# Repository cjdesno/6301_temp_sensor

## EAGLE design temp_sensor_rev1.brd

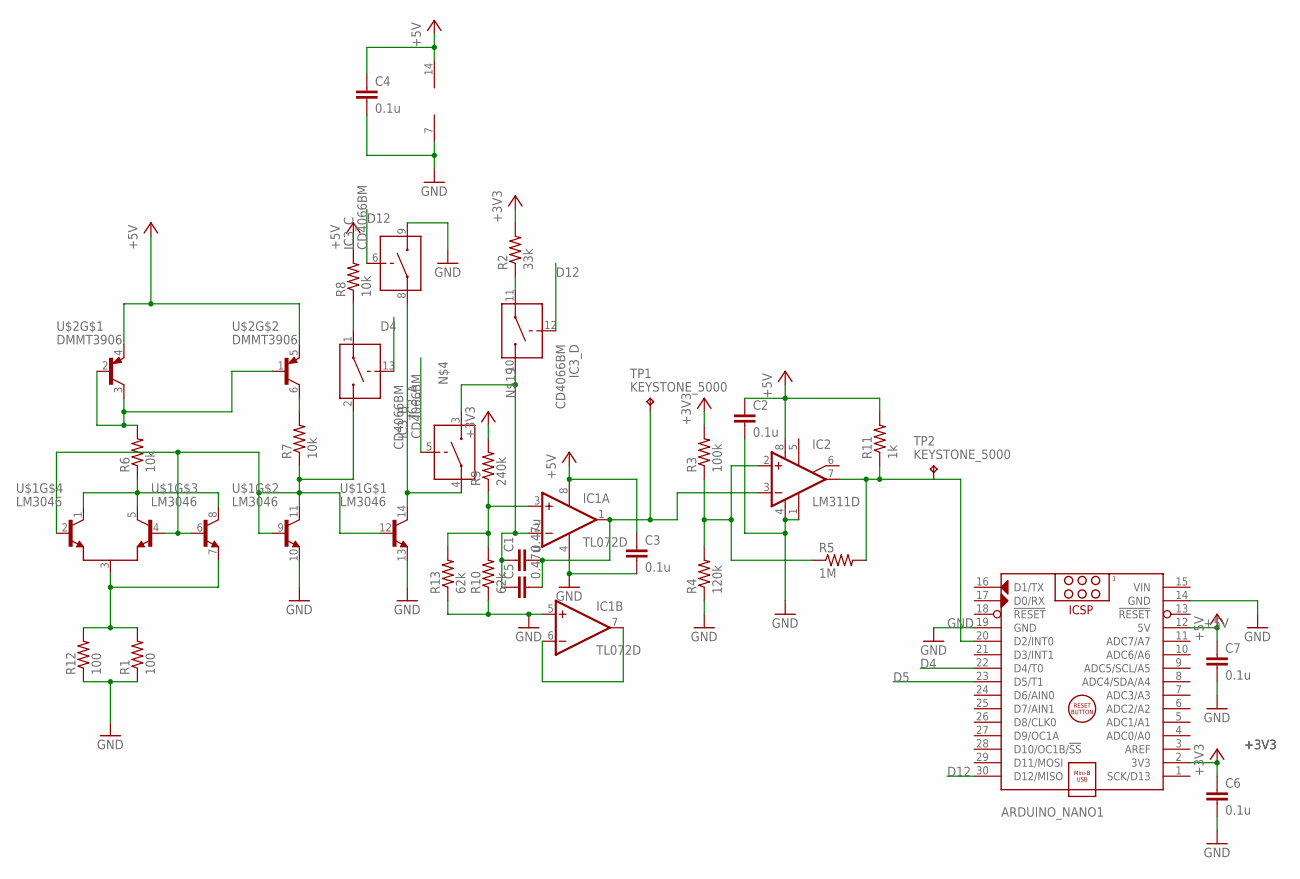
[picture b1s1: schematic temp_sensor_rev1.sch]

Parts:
ARDUINO_NANO1: ARDUINO_NANO
C1: 0.47u; C1206
C2, C3, C4, C6, C7: 0.1u; C0805
C5: 0.47u; C2.5-2
IC1: TL072D; SO08
IC2: LM311D; SO08
IC3: CD4066BM; SO14
R1: 100; M1206
R2: 33k; M1206
R3: 100k; M1206
R4: 120k; M1206
R5: 1M; M1206
R6, R7, R8: 10k; M1206
R9: 240k; M1206
R10: 62k; M1206
R11: 1k; M1206
R12: 100; 0207/7
R13: 62k; 0207/7
TP1, TP2: KEYSTONE_5000; KEYSTONE_5000_MINIATURE
U$1: LM3046; SO14
U$2: DMMT3906; SOT363_PHILIPS

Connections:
+3V3: ARDUINO_NANO1.2 (3V3), C6.1, R2.2, R3.2, R9.2
+5V: ARDUINO_NANO1.12 (5V), C2.1, C3.1, C4.1, C7.1, IC1.8 (V+), IC2.8 (V+), IC3.14 (V+), R8.2, R11.2, U$2.4 (E), U$2.5 (E)
D4: ARDUINO_NANO1.22 (D4/T0), IC3.13 (CONTROL)
D5: ARDUINO_NANO1.23 (D5/T1), IC3.5 (CONTROL)
D12: ARDUINO_NANO1.30 (D12/MISO), IC3.6 (CONTROL), IC3.12 (CONTROL)
GND: ARDUINO_NANO1.14 (GND), ARDUINO_NANO1.19 (GND), C2.2, C3.2, C4.2, C6.2, C7.2, IC1.4 (V-), IC1.5 (+IN), IC2.1 (GND), IC2.4 (V-), IC3.7 (V-), IC3.9 (IN/OUT2), R1.1, R4.1, R10.1, R12.1, R13.1, U$1.10 (E), U$1.13 (E)
unnamed: IC1.6 (-IN), IC1.7 (OUT)
unnamed: R1.2, R12.2, U$1.3 (E), U$1.7 (E)
unnamed: IC3.4 (IN/OUT1), IC3.8 (IN/OUT1), U$1.14 (C)
unnamed: ARDUINO_NANO1.20 (D2/INT0), IC2.7 (OUT), R5.2, R11.1, TP2.P$1
unnamed: IC2.2 (+IN), R3.1, R4.2, R5.1
unnamed: R6.1, U$1.1 (C), U$1.5 (CR), U$1.8 (C)
unnamed: R6.2, U$2.1 (B), U$2.2 (B), U$2.3 (C)
unnamed: R7.2, U$2.6 (C)
unnamed: IC3.2 (IN/OUT2), R7.1, U$1.2 (B), U$1.4 (BR), U$1.6 (B), U$1.9 (B), U$1.11 (C), U$1.12 (B)
unnamed: IC3.1 (IN/OUT1), R8.1
unnamed: IC1.3 (+IN), R9.1, R10.2, R13.2
unnamed: IC3.11 (IN/OUT1), R2.1
unnamed: C1.1, C5.1, IC1.2 (-IN), IC3.3 (IN/OUT2), IC3.10 (IN/OUT2)
unnamed: C1.2, C5.2, IC1.1 (OUT), IC2.3 (-IN), TP1.P$1
VIN: ARDUINO_NANO1.15 (VIN)

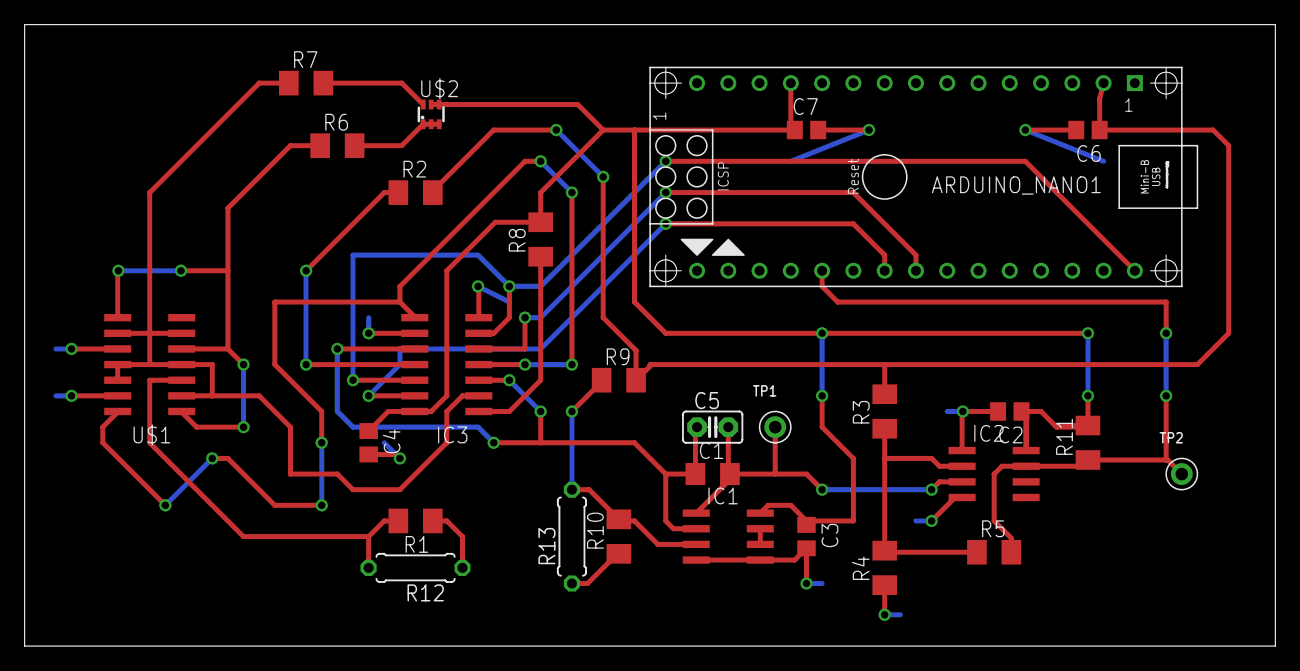
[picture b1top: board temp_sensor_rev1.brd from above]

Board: 2 copper layers, 101.6 x 50.5 mm, 28 parts (0 on the bottom side), 20 nets.

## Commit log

2016-12-13 PCB files added
